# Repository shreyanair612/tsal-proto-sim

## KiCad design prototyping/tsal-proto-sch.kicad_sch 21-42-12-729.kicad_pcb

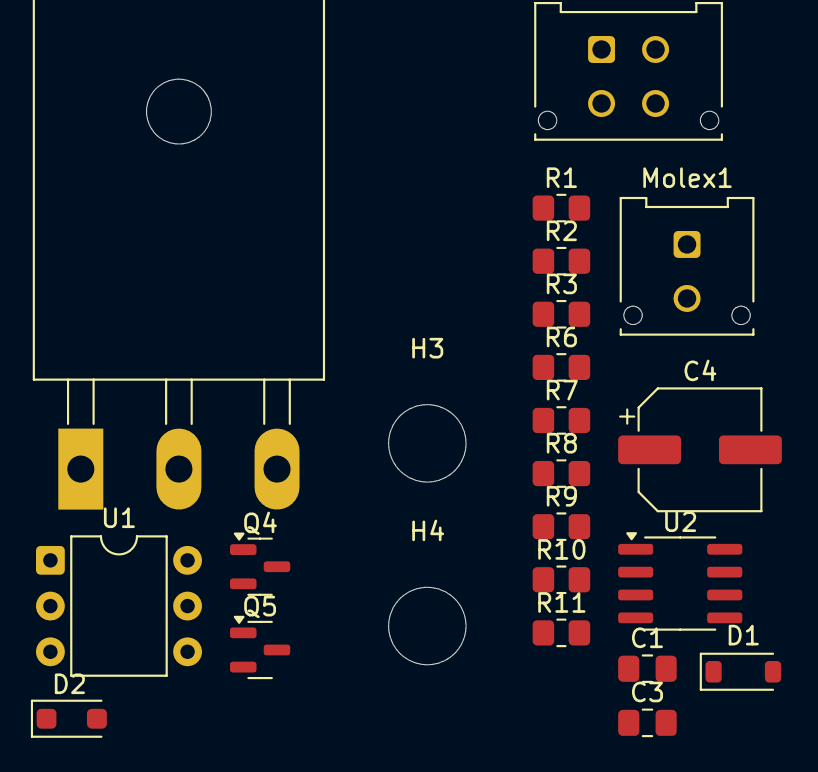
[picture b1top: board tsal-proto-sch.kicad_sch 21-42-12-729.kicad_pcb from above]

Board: 2 copper layers, 25 parts (0 on the bottom side), 18 nets, no tracks yet.

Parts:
C1: 0.1uF; C_0805_2012Metric_Pad1.18x1.45mm_HandSolder
C3: 1uF; C_0805_2012Metric_Pad1.18x1.45mm_HandSolder
C4: 100uF; CP_Elec_6.3x5.4
D1: BZT52C12; D_SOD-123
D2: BZT52C51; D_SOD-123F
H1, H2, H3, H4: MountingHole; MountingHole_4.3mm_M4
J1: 043045-0412; Molex_Micro-Fit_3.0_43045-0412_2x02_P3.00mm_Vertical
Molex1: 043045-0212; Molex_Micro-Fit_3.0_43045-0212_2x01_P3.00mm_Vertical
Q3: UJ3N065080K3S; TO-247-3_Horizontal_TabDown
Q4: DMN2056U; SOT-23
Q5: AO3401A; SOT-23
R1, R8: 10k; R_0805_2012Metric_Pad1.20x1.40mm_HandSolder
R2, R9, R10, R11: 240k; R_0805_2012Metric_Pad1.20x1.40mm_HandSolder
R3: 2M; R_0805_2012Metric_Pad1.20x1.40mm_HandSolder
R6: 5.6k; R_0805_2012Metric_Pad1.20x1.40mm_HandSolder
R7: 3k; R_0805_2012Metric_Pad1.20x1.40mm_HandSolder
U1: H11L1M; DIP-6_W7.62mm
U2: NE555D; SOIC-8_3.9x4.9mm_P1.27mm

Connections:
/HV-: D1.2 (A), Q3.1 (G), Q4.2 (S), R3.2
GLV+: C3.2, J1.1, Q5.2 (S), R1.1, U1.6, U2.8 (VCC)
GND: C1.1, C3.1, C4.2, J1.2, J1.4, R8.1, U1.5, U2.1 (GND)
Light+: J1.3, Q5.3 (D)
unnamed: D1.1 (K), Q4.1 (G), R3.1, R11.2
unnamed: D2.2 (A), R2.1
unnamed: D2.1 (K), Q3.2 (D)
unnamed: R8.2, U2.4 (R)
unnamed: R1.2, U1.4
unnamed: Q3.3 (S), R6.1
unnamed: Q4.3 (D), U1.2
unnamed: Q5.1 (G), R7.2, U2.3 (Q), U2.7 (DIS)
unnamed: R2.2, R9.1
unnamed: R6.2, U1.1
unnamed: R9.2, R10.1
unnamed: R10.2, R11.1
unnamed: C1.2, U2.5 (CV)
unnamed: C4.1, R7.1, U2.2 (TR), U2.6 (THR)

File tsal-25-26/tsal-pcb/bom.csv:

Designator,Footprint,Quantity,Value,LCSC Part #
C1,0805,1,0.1uF,
C3,0805,1,1uF,
C4,CP_Elec_6.3x5.4,1,100uF,
D1,D_SOD-123,1,BZT52C12,
D2,D_SOD-123F,1,BZT52C51,
"F1, F2",1206,2,750mA,
J1,Molex_Micro-Fit_3.0_43045-0412_2x02_P3.00mm_Vertical,1,043045-0412,
MOLEX1,Molex_Micro-Fit_3.0_43045-0212_2x01_P3.00mm_Vertical,1,043045-0212,
Q1,SOT-23,1,DMP2035U-7,
Q3,TO-247-3_Horizontal_TabDown,1,UJ3N065080K3S,
Q4,SOT-23,1,DMN2056U,
Q5,SOT-23,1,AO3401A,
R1,0805,1,2k,
"R10, R11, R2, R9",0805,4,240k,
R3,0805,1,2M,
R5,0805,1,5k,
R6,0805,1,5.6k,
R7,0805,1,3k,
R8,0805,1,1k,
U1,DIP-6_W7.62mm,1,H11L1M,
U2,SOIC-8_3.9x4.9mm_P1.27mm,1,NE555D,

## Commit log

2025-09-14 started working on model
2025-09-14 finished ne555 model
2025-09-14 cannot open include file
2025-09-16 replaced with internal circuit
2025-09-16 git pushing again2.0
2025-09-16 trying to sim on different device
2025-09-16 added working 555 sim
2025-09-16 replaced tsal-sim with correct sch
2025-09-16 naming conventions
2025-09-16 condensed design
2025-09-17 timer frequency, output diode, reset signal input
2025-09-17 completed circuit sim
2025-09-18 files cleaned up
2025-09-18 added pcb file
2025-09-18 netlist for pcb added
2025-09-18 simulation tests voltage cutoff
2025-09-23 TSAL_rdy4pcb
2025-09-23 updated pcb-24-25 to have new sch and applied to pcb
2025-09-23 deleted new because pcb-24-25 is being updated directly
2025-09-25 final 25-26 files
2025-09-25 final 25-26
2025-09-30 new pcb with correct dimensions
2025-09-30 new tsal pcb resized
